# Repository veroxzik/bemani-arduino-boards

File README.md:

# bemani-arduino-boards
 A collection of Arduuino breakout boards and code for Bemani uses.

## How to Order

Download the *.zip file from your chosen Boards/gerbers folder and upload to your PCB manufacturer of choice. JLCPCB is a common suggestion and the one I use most frequently. Default choices are all acceptable.

A list of parts for each board is located in their respective folders.

## Physical Settings on the Boards

Each board has a few physical solder jumpers that you must set before use.

### Setting the lights power source

Locate the jumper labeled CNR PWR | USB PWR. If you wish to power the lights off of USB power, jump the center pad and the USB PWR pad together.

If you wish to use the external power header, jump the center pad and the CNR PWR pad together. All external power headers are such that the square pin is positive.

On several boards, it is necessary to select whether you want to use encoders or buttons. Such option is used by soldering the *two* jumpers between either BUT or ENC.

On the Micro boards, if you use one encoder, it must be QE2. On the Pro Micro board, it must be QE1. (Or you can change my code if you don't like this restriction.)

## How to Flash Firmware

### Load the board profile

Move the folder `Additional Files\arduino-bemani` to your local hardware folder, most commonly located at `Documents\Arduino\hardware\`.
Your final path should look like `Documents\Arduino\hardware\arduino-bemani`.

Start the Arduino IDE / restart if it's already open.

This uses a copy of the Arduino 1.8.1 core, for reference. You should not have to update it.

### Loading the firmware

In the Arduino IDE, select the board using `Tools->Board->Bemani Controller (Micro/Pro Micro)` under the `VXZK Custom Boards` section.

In `Config.h`, set the following parameters per your board and setup.

```c
/* --- --- --- --- --- --- ---
   Frequently Changed Settings
   --- --- --- --- --- --- --- */

// This is the number of encoders you are using.
// If it is 1 and you are using a Micro board, then you must use QE2.
// If it is 1 and you are using a Pro Micro board, then you must use QE1
#define NUM_ENCODERS 0

// This is the PPR of your encoder
// Common values are 600 for Chinese encoders and 24 for Bourns encoders
const uint16_t pulseCount = 24;

// Uncomment the corresponding define for the microcontroller you are using
//#define USE_PROMICRO
//#define USE_MICRO
```

You must uncomment either the USE_PROMICRO or USE_MICRO define or the compiler will throw an error.

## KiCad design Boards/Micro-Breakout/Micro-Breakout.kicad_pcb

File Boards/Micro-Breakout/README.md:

# Micro Breakout

## Description

This board uses the Arduino Micro as its base and supports 4 pin button connectors using the DJ DAO layout.

It is configurable for one of the three options:
1. 12 buttons, no encoders
2. 11 buttons, 1 encoder
3. 10 buttons, 2 encoders

## Bill of Materials

| Part | Description | Qty | Link |
|:---|:---|:---:|:---|
| Arduino Micro | Microprocessor | 1 | Search "Arduino Micro" on Aliexpress, ensure the listing says 32U4. Example listing: https://www.aliexpress.us/item/2251801707415032.html |
| JST XH 4P Header | Connector for buttons, encoders, and RGB | 14 | https://www.lcsc.com/product-detail/Wire-To-Board-Wire-To-Wire-Connector_BOOMELE-Boom-Precision-Elec-XH-4A_C37815.html |
| 2N7000 | MOSFET 60V 0.2A N-Channel TO-92 | 12 | https://www.lcsc.com/product-detail/MOSFETs_Jiangsu-Changjing-Electronics-Technology-Co-Ltd-2N7000_C9114.html |
| JST XH 2P Header | Connector for external power (optional) | 1 (optional) | https://www.lcsc.com/product-detail/Wire-To-Board-Wire-To-Wire-Connector_BOOMELE-Boom-Precision-Elec-XH-2A_C20079.html |

Connectors can also be found on Aliexpress by searching "JST XH".

## Configuration

### Power Selection

Typically, you will be using USB power for this board. Solder the middle and left pads together on jumper located at the top of the board.

By soldering the other two pads, the LEDs will be powered via the JST XH 2P connector. This can allow you to use 12V leds, if this is desired.

### Button and Encoder Selection

Next to each QE connector is a pair of solder jumpers.

To use QE1, solder the middle and top pads together for the marked jumpers. Otherwise, solder the middle and bottom pads to use Button 10.

To use QE2, solder the middle and top pads together for the marked jumpers. Otherwise, solder the middle and bottom pads to use Button 11.

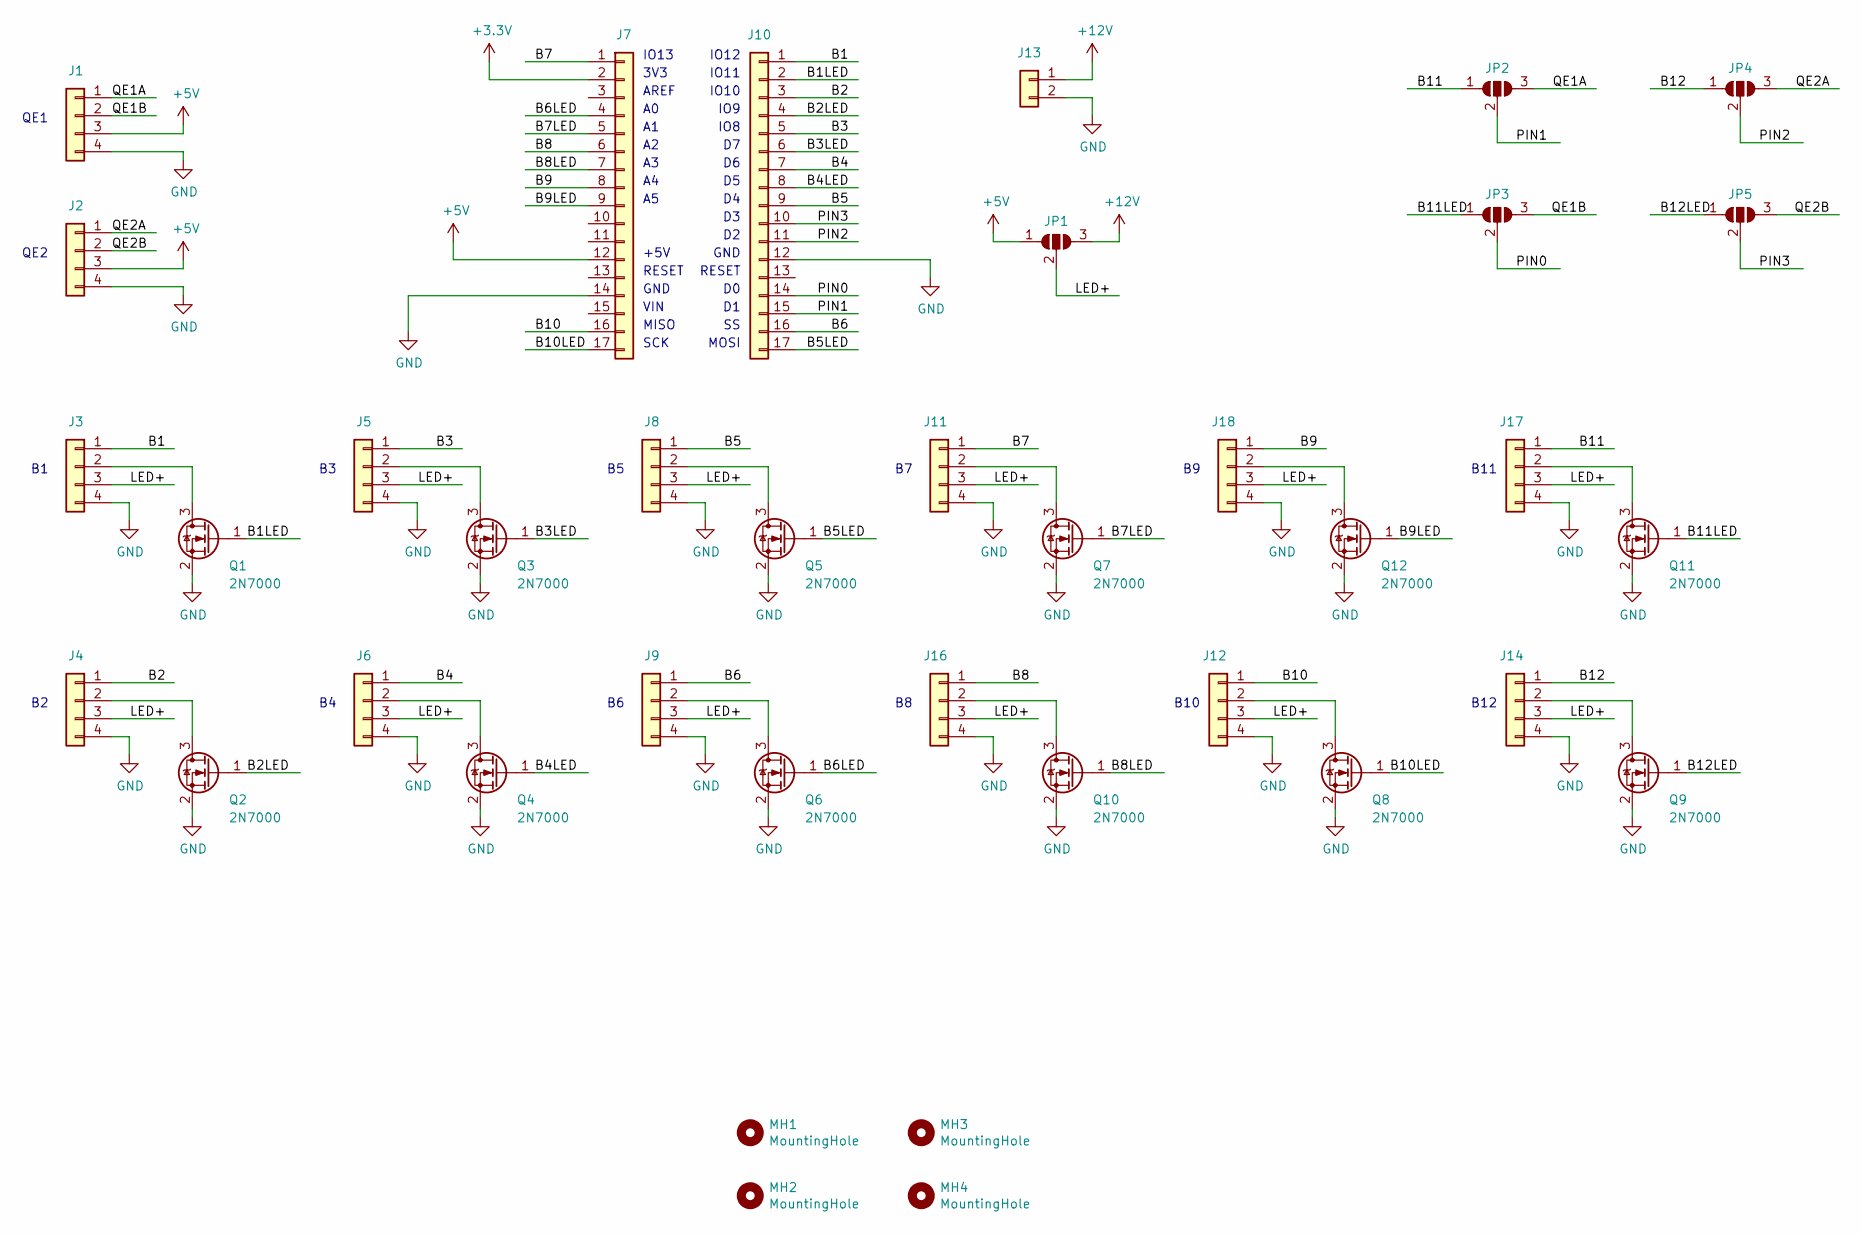
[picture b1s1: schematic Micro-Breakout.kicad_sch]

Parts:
J1, J2, J3, J4, J5, J6, J8, J9, J11, J12, J14, J16, J17, J18: Conn_01x04; JST_XH_B4B-XH-A_1x04_P2.50mm_Vertical
J7, J10: Conn_01x17; PinSocket_1x17_P2.54mm_Vertical
J13: Conn_01x02; JST_XH_B2B-XH-A_1x02_P2.50mm_Vertical
JP1, JP2, JP3, JP4, JP5: SolderJumper_3_Open; SolderJumper-3_P1.3mm_Open_RoundedPad1.0x1.5mm
MH1, MH2, MH3, MH4: MountingHole; MountingHole_3.2mm_M3
Q1, Q2, Q3, Q4, Q5, Q6, Q7, Q8, Q9, Q10, Q11, Q12: 2N7000; TO-92_Inline_Wide

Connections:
+3V3: J7.2
+5V: J1.3, J2.3, J7.12, JP1.1 (A)
+12V: J13.1, JP1.3 (B)
/B1: J3.1, J10.1
/B1LED: J10.2, Q1.1 (G)
/B2: J4.1, J10.3
/B2LED: J10.4, Q2.1 (G)
/B3: J5.1, J10.5
/B3LED: J10.6, Q3.1 (G)
/B4: J6.1, J10.7
/B4LED: J10.8, Q4.1 (G)
/B5: J8.1, J10.9
/B5LED: J10.17, Q5.1 (G)
/B6: J9.1, J10.16
/B6LED: J7.4, Q6.1 (G)
/B7: J7.1, J11.1
/B7LED: J7.5, Q7.1 (G)
/B8: J7.6, J16.1
/B8LED: J7.7, Q10.1 (G)
/B9: J7.8, J18.1
/B9LED: J7.9, Q12.1 (G)
/B10: J7.16, J12.1
/B10LED: J7.17, Q8.1 (G)
/B11: J17.1, JP2.1 (A)
/B11LED: JP3.1 (A), Q11.1 (G)
/B12: J14.1, JP4.1 (A)
/B12LED: JP5.1 (A), Q9.1 (G)
/LED+: J3.3, J4.3, J5.3, J6.3, J8.3, J9.3, J11.3, J12.3, J14.3, J16.3, J17.3, J18.3, JP1.2 (C)
/PIN0: J10.14, JP3.2 (C)
/PIN1: J10.15, JP2.2 (C)
/PIN2: J10.11, JP4.2 (C)
/PIN3: J10.10, JP5.2 (C)
/QE1A: J1.1, JP2.3 (B)
/QE1B: J1.2, JP3.3 (B)
/QE2A: J2.1, JP4.3 (B)
/QE2B: J2.2, JP5.3 (B)
GND: J1.4, J2.4, J3.4, J4.4, J5.4, J6.4, J7.14, J8.4, J9.4, J10.12, J11.4, J12.4, J13.2, J14.4, J16.4, J17.4, J18.4, Q1.2 (S), Q2.2 (S), Q3.2 (S), Q4.2 (S), Q5.2 (S), Q6.2 (S), Q7.2 (S), Q8.2 (S), Q9.2 (S), Q10.2 (S), Q11.2 (S), Q12.2 (S)
unnamed: J3.2, Q1.3 (D)
unnamed: J4.2, Q2.3 (D)
unnamed: J5.2, Q3.3 (D)
unnamed: J6.2, Q4.3 (D)
unnamed: J8.2, Q5.3 (D)
unnamed: J9.2, Q6.3 (D)
unnamed: J11.2, Q7.3 (D)
unnamed: J12.2, Q8.3 (D)
unnamed: J14.2, Q9.3 (D)
unnamed: J16.2, Q10.3 (D)
unnamed: J17.2, Q11.3 (D)
unnamed: J18.2, Q12.3 (D)

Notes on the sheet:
IO11
B12
QE1
QE2
VIN
GND
3V3
IO9
MOSI
+5V
RESET
MISO
SCK
IO8
IO13
B11
IO10
B10
IO12
AREF

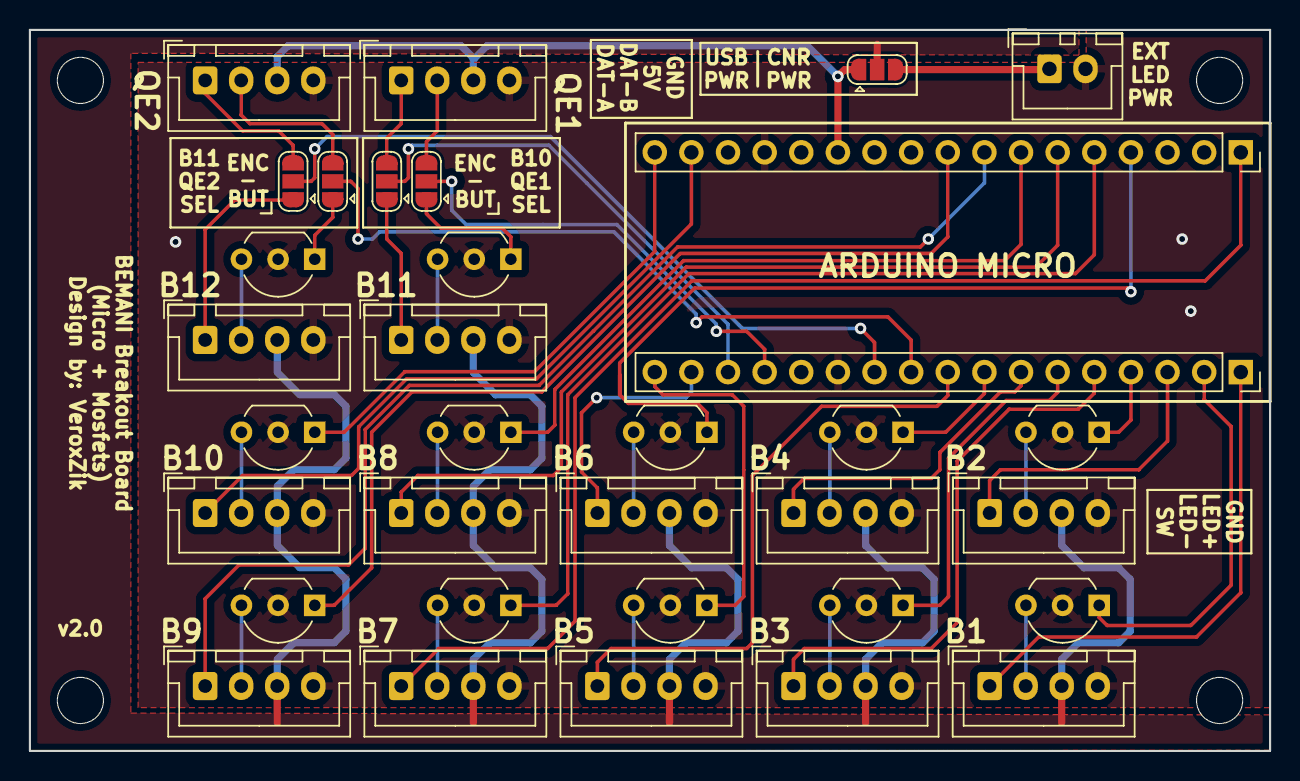
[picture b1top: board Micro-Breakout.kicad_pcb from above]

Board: 2 copper layers, 86.0 x 50.0 mm, 38 parts (0 on the bottom side), 48 nets.

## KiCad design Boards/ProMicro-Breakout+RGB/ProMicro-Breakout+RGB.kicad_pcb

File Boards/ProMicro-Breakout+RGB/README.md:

# ProMicro Breakout + RGB

## Description

This board is just for the bare essentials, providing 12 buttons (WITHOUT lights), 2 quadrature encoder inputs, and 1 ARGB header.

## Bill of Materials

| Part | Description | Qty | Link |
|:---|:---|:---:|:---|
| Arduino Pro Micro | Microprocessor | 1 | Search "Pro Micro" on Aliexpress, ensure the listing says 32U4 |
| JST XH 2P Header | Connector for buttons and power (optional) | 12 (+ 1 optional) | https://www.lcsc.com/product-detail/Wire-To-Board-Wire-To-Wire-Connector_BOOMELE-Boom-Precision-Elec-XH-2A_C20079.html |
| JST XH 4P Header | Connector for encoder and RGB | 3 | https://www.lcsc.com/product-detail/Wire-To-Board-Wire-To-Wire-Connector_BOOMELE-Boom-Precision-Elec-XH-4A_C37815.html |

Connectors can also be found on Aliexpress by searching "JST XH".

## Configuration

### Power Selection

Typically, you will be using USB power for this board. Solder the middle and right pads together on jumper JP1.

By soldering the other two pads, the LEDs will be powered via the JST XH 2P connector. This can allow you to use 12V leds, if this is desired.

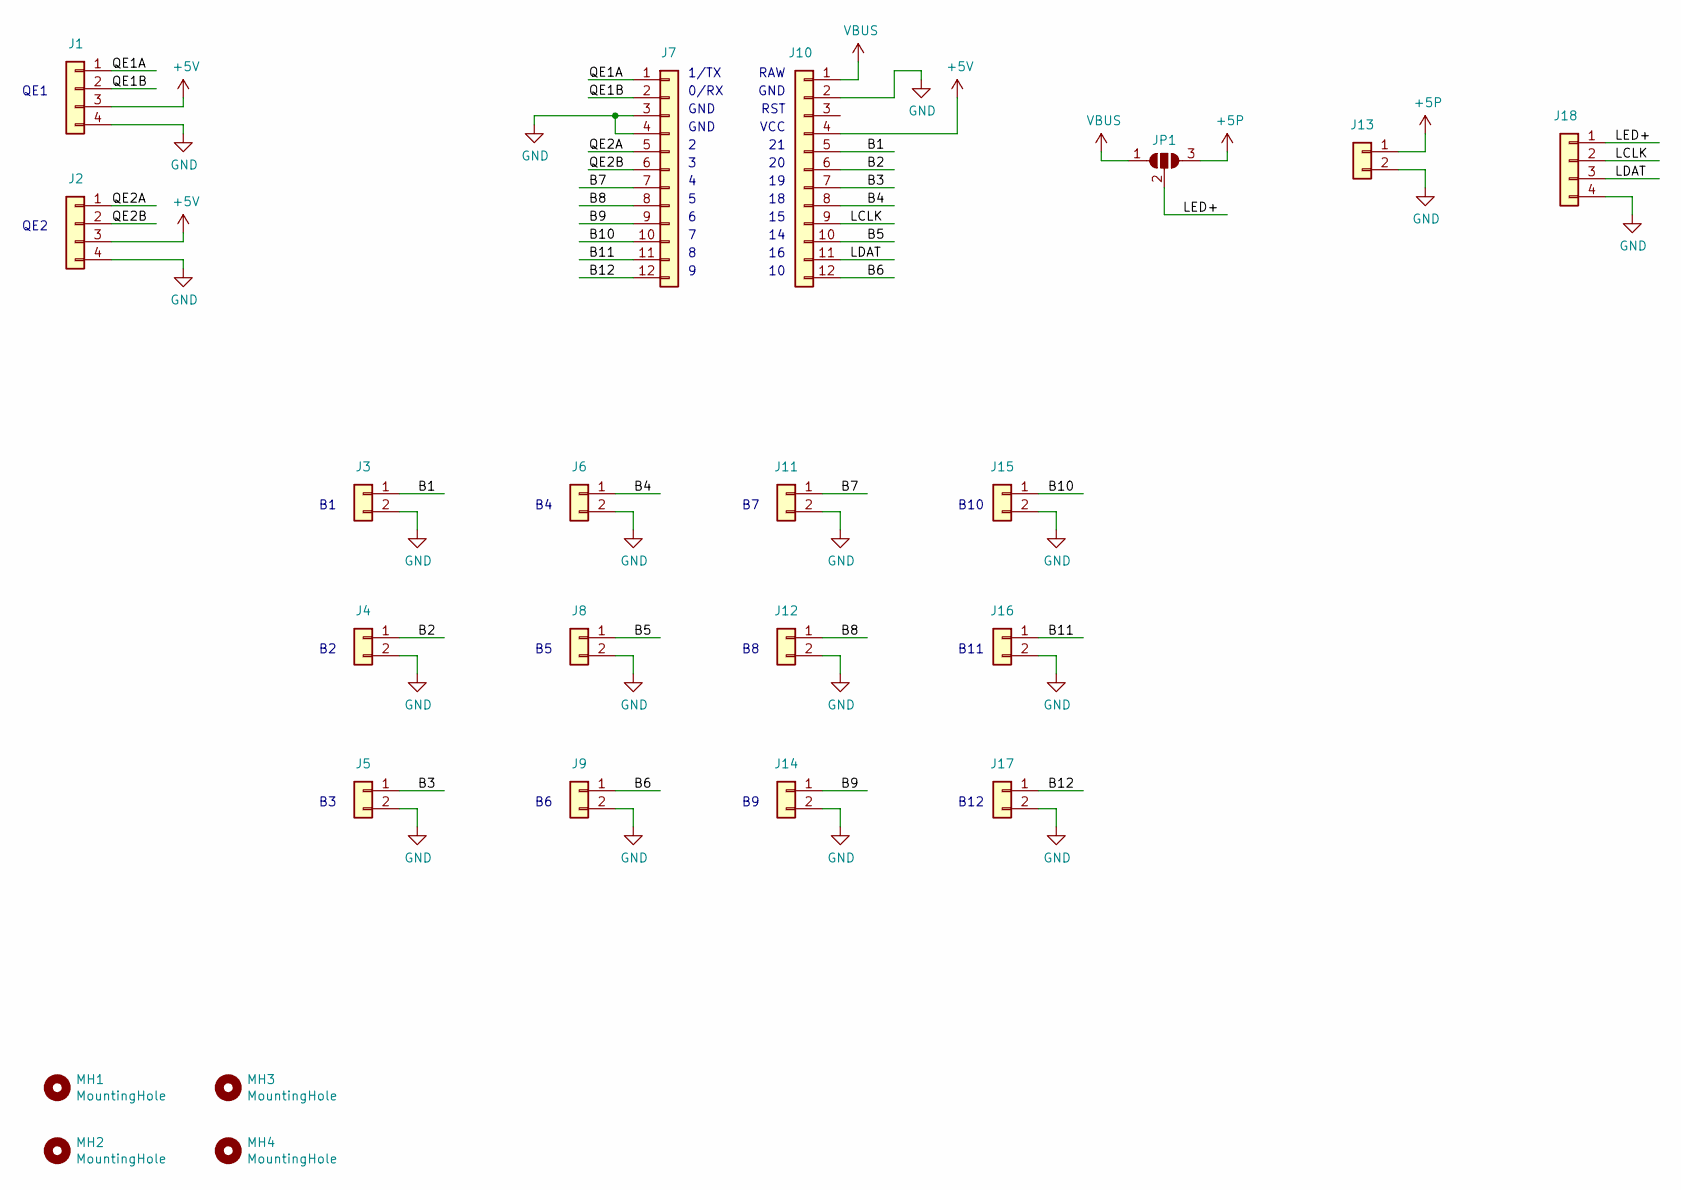
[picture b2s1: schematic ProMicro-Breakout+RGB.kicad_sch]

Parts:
J1, J2, J18: Conn_01x04; JST_XH_B04B-XH-A_04x2.50mm_Straight
J3, J4, J5, J6, J8, J9, J11, J12, J13, J14, J15, J16, J17: Conn_01x02; JST_XH_B02B-XH-A_02x2.50mm_Straight
J7, J10: Conn_01x12; PinSocket_1x12_P2.54mm_Vertical
JP1: SolderJumper_3_Open; SolderJumper-3_P1.3mm_Open_RoundedPad1.0x1.5mm
MH1, MH2, MH3, MH4: MountingHole; MountingHole_3.2mm_M3

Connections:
+5P: J13.1, JP1.3 (B)
+5V: J1.3, J2.3, J10.4
/B1: J3.1, J10.5
/B2: J4.1, J10.6
/B3: J5.1, J10.7
/B4: J6.1, J10.8
/B5: J8.1, J10.10
/B6: J9.1, J10.12
/B7: J7.7, J11.1
/B8: J7.8, J12.1
/B9: J7.9, J14.1
/B10: J7.10, J15.1
/B11: J7.11, J16.1
/B12: J7.12, J17.1
/LCLK: J10.9, J18.2
/LDAT: J10.11, J18.3
/LED+: J18.1, JP1.2 (C)
/QE1A: J1.1, J7.1
/QE1B: J1.2, J7.2
/QE2A: J2.1, J7.5
/QE2B: J2.2, J7.6
GND: J1.4, J2.4, J3.2, J4.2, J5.2, J6.2, J7.3, J7.4, J8.2, J9.2, J10.2, J11.2, J12.2, J13.2, J14.2, J15.2, J16.2, J17.2, J18.4
VBUS: J10.1, JP1.1 (A)

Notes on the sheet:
B12
QE2
B11
GND
B10
0/RX
VCC
QE1
1/TX
RST
RAW

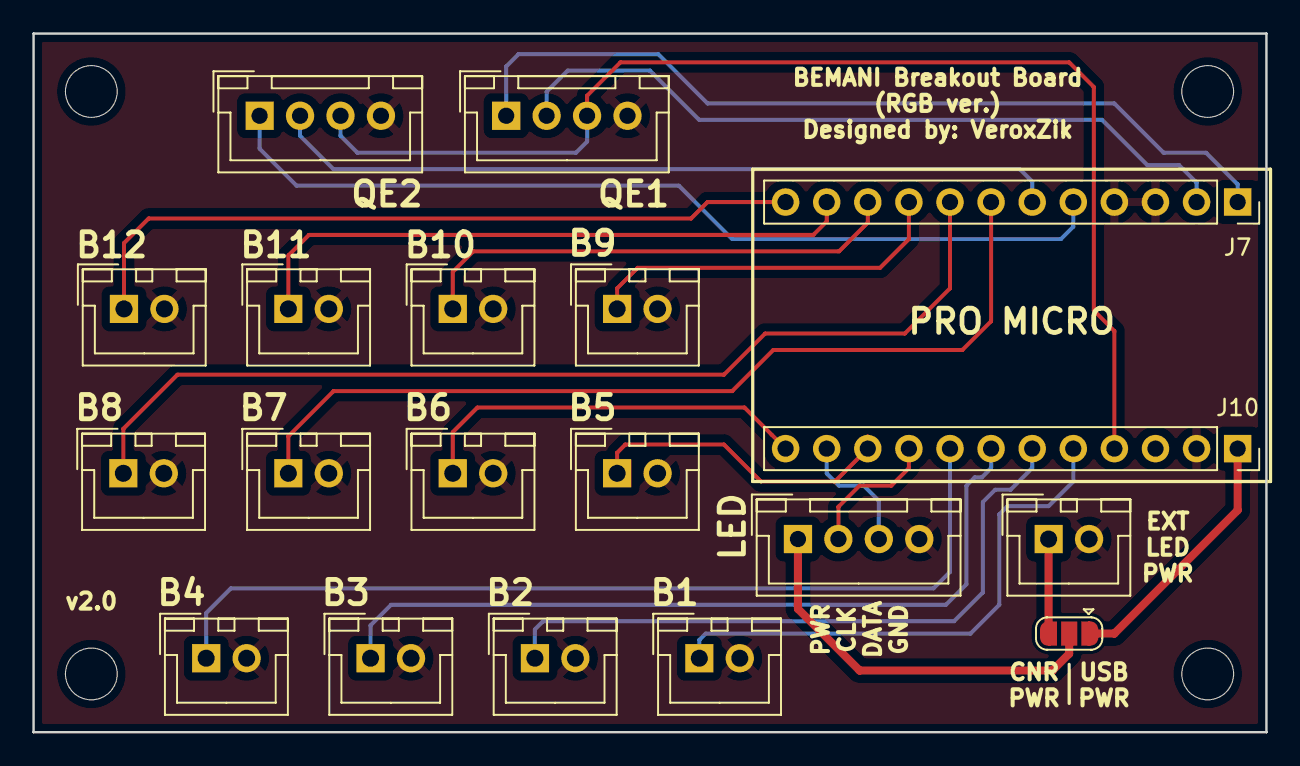
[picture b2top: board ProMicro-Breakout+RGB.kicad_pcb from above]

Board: 2 copper layers, 76.2 x 43.2 mm, 23 parts (0 on the bottom side), 23 nets.

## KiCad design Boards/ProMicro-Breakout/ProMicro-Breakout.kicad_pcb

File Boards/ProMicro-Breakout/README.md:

# ProMicro Breakout

## Description

This board uses the Sparkfun Pro Micro as its base and supports 4 pin button connectors using the DJ DAO layout.

It is configurable for one of the three options:
1. 9 buttons, no encoders
2. 8 buttons, 1 encoder
3. 7 buttons, 2 encoders

## Bill of Materials

| Part | Description | Qty | Link |
|:---|:---|:---:|:---|
| Arduino Pro Micro | Microprocessor | 1 | Search "Pro Micro" on Aliexpress, ensure the listing says 32U4 |
| JST XH 4P Header | Connector for buttons and encoder | 11 | https://www.lcsc.com/product-detail/Wire-To-Board-Wire-To-Wire-Connector_BOOMELE-Boom-Precision-Elec-XH-4A_C37815.html |
| JST XH 2P Header | Connector for external power (optional) | 1 (optional) | https://www.lcsc.com/product-detail/Wire-To-Board-Wire-To-Wire-Connector_BOOMELE-Boom-Precision-Elec-XH-2A_C20079.html |
| 2N7000 | MOSFET 60V 0.2A N-Channel TO-92 | 9 | https://www.lcsc.com/product-detail/MOSFETs_Jiangsu-Changjing-Electronics-Technology-Co-Ltd-2N7000_C9114.html |

Connectors can also be found on Aliexpress by searching "JST XH".

## Configuration

### Power Selection

Typically, you will be using USB power for this board. Solder the middle and right pads together on jumper JP1.

By soldering the other two pads, the LEDs will be powered via the JST XH 2P connector. This can allow you to use 12V leds, if this is desired.

### Button and Encoder Selection

Next to each QE connector is a pair of solder jumpers.

To use QE1, solder the middle and right pads together for jumpers JP2 and JP3. Otherwise, solder the middle and left pads to use Button 9.

To use QE2, solder the middle and right pads together for jumpers JP4 and JP5. Otherwise, solder the middle and left pads to use Button 8.

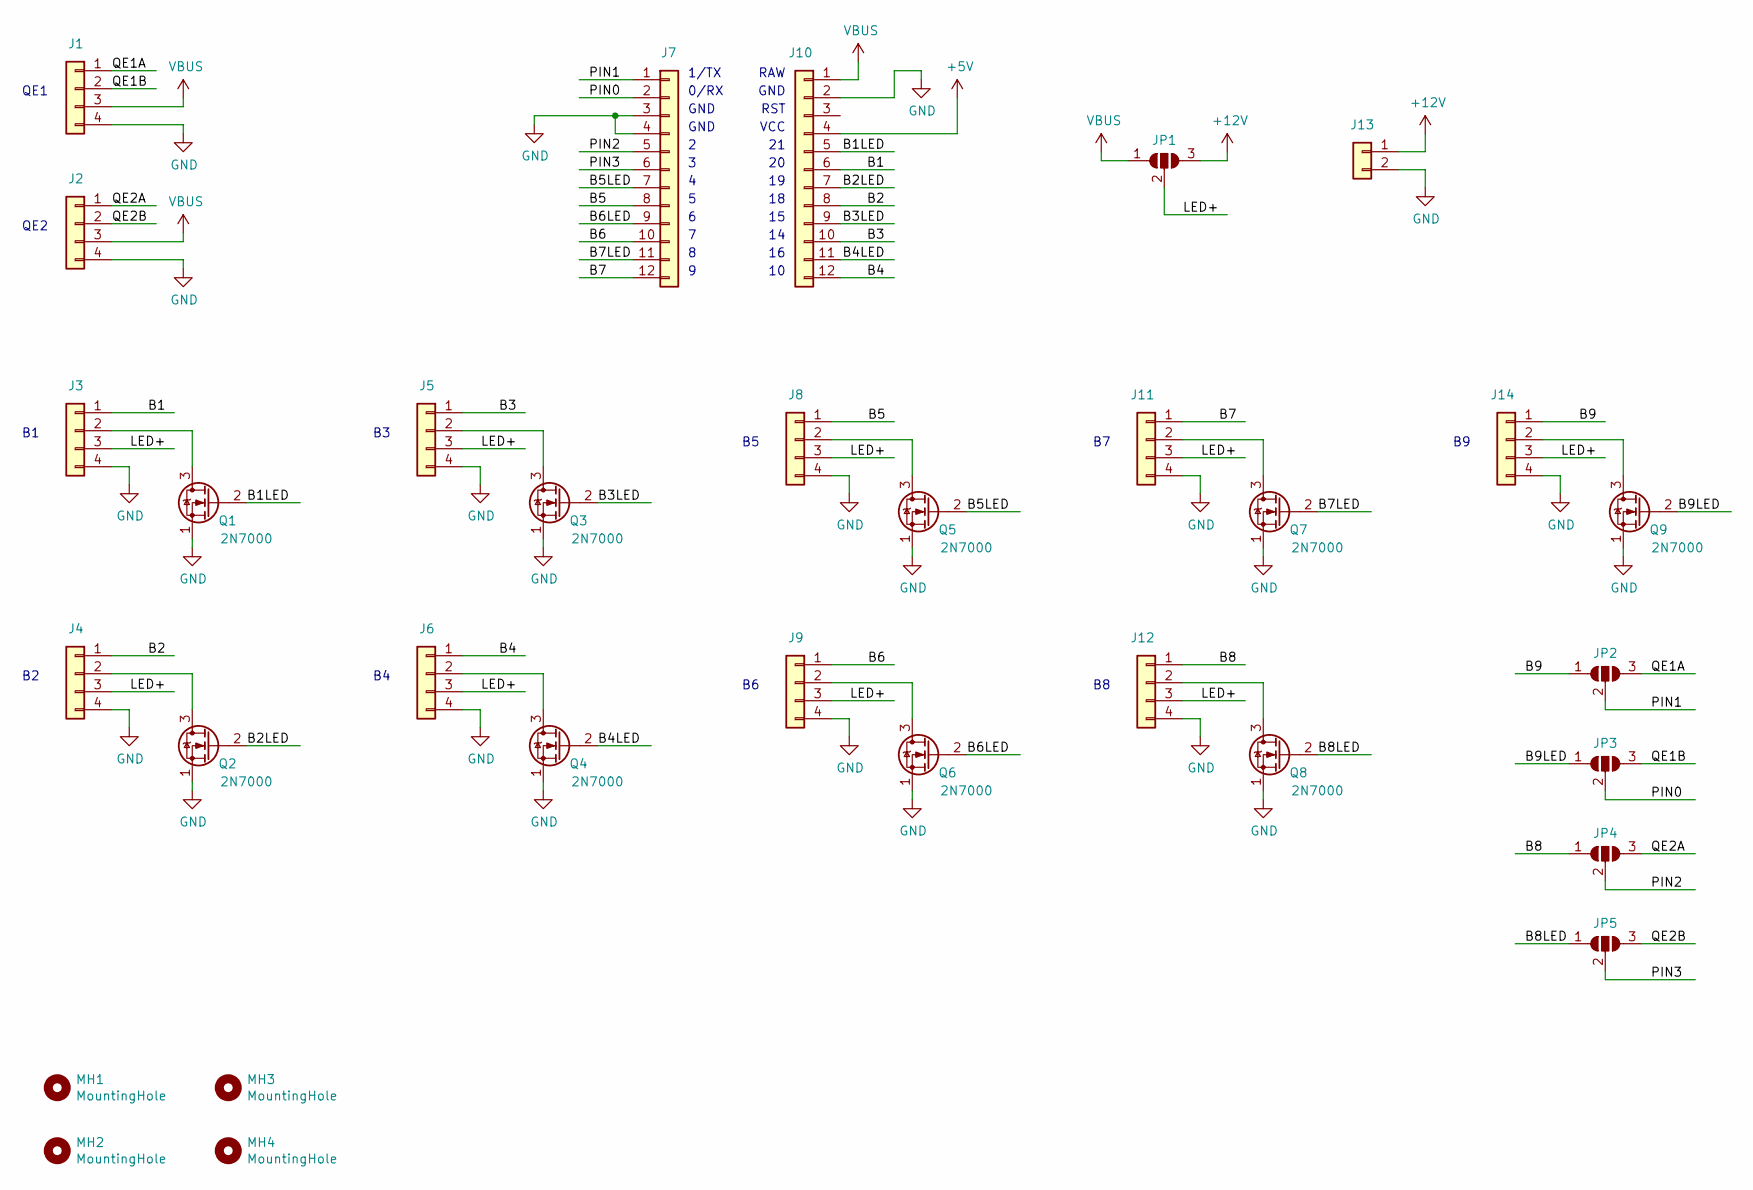
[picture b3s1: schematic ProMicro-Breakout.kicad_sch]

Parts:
J1, J2, J3, J4, J5, J6, J8, J9, J11, J12, J14: Conn_01x04; JST_XH_B04B-XH-A_04x2.50mm_Straight
J7, J10: Conn_01x12; PinSocket_1x12_P2.54mm_Vertical
J13: Conn_01x02; JST_XH_B02B-XH-A_02x2.50mm_Straight
JP1, JP2, JP3, JP4, JP5: SolderJumper_3_Open; SolderJumper-3_P1.3mm_Open_RoundedPad1.0x1.5mm
MH1, MH2, MH3, MH4: MountingHole; MountingHole_3.2mm_M3
Q1, Q2, Q3, Q4, Q5, Q6, Q7, Q8, Q9: 2N7000; TO-92_Inline_Wide

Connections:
+5V: J10.4
+12V: J13.1, JP1.3 (B)
/B1: J3.1, J10.6
/B1LED: J10.5, Q1.2 (G)
/B2: J4.1, J10.8
/B2LED: J10.7, Q2.2 (G)
/B3: J5.1, J10.10
/B3LED: J10.9, Q3.2 (G)
/B4: J6.1, J10.12
/B4LED: J10.11, Q4.2 (G)
/B5: J7.8, J8.1
/B5LED: J7.7, Q5.2 (G)
/B6: J7.10, J9.1
/B6LED: J7.9, Q6.2 (G)
/B7: J7.12, J11.1
/B7LED: J7.11, Q7.2 (G)
/B8: J12.1, JP4.1 (A)
/B8LED: JP5.1 (A), Q8.2 (G)
/B9: J14.1, JP2.1 (A)
/B9LED: JP3.1 (A), Q9.2 (G)
/LED+: J3.3, J4.3, J5.3, J6.3, J8.3, J9.3, J11.3, J12.3, J14.3, JP1.2 (C)
/PIN0: J7.2, JP3.2 (C)
/PIN1: J7.1, JP2.2 (C)
/PIN2: J7.5, JP4.2 (C)
/PIN3: J7.6, JP5.2 (C)
/QE1A: J1.1, JP2.3 (B)
/QE1B: J1.2, JP3.3 (B)
/QE2A: J2.1, JP4.3 (B)
/QE2B: J2.2, JP5.3 (B)
GND: J1.4, J2.4, J3.4, J4.4, J5.4, J6.4, J7.3, J7.4, J8.4, J9.4, J10.2, J11.4, J12.4, J13.2, J14.4, Q1.1 (S), Q2.1 (S), Q3.1 (S), Q4.1 (S), Q5.1 (S), Q6.1 (S), Q7.1 (S), Q8.1 (S), Q9.1 (S)
unnamed: J3.2, Q1.3 (D)
unnamed: J4.2, Q2.3 (D)
unnamed: J5.2, Q3.3 (D)
unnamed: J6.2, Q4.3 (D)
unnamed: J8.2, Q5.3 (D)
unnamed: J9.2, Q6.3 (D)
unnamed: J11.2, Q7.3 (D)
unnamed: J12.2, Q8.3 (D)
unnamed: J14.2, Q9.3 (D)
VBUS: J1.3, J2.3, J10.1, JP1.1 (A)

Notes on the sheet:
RAW
RST
QE1
GND
QE2
1/TX
VCC
0/RX

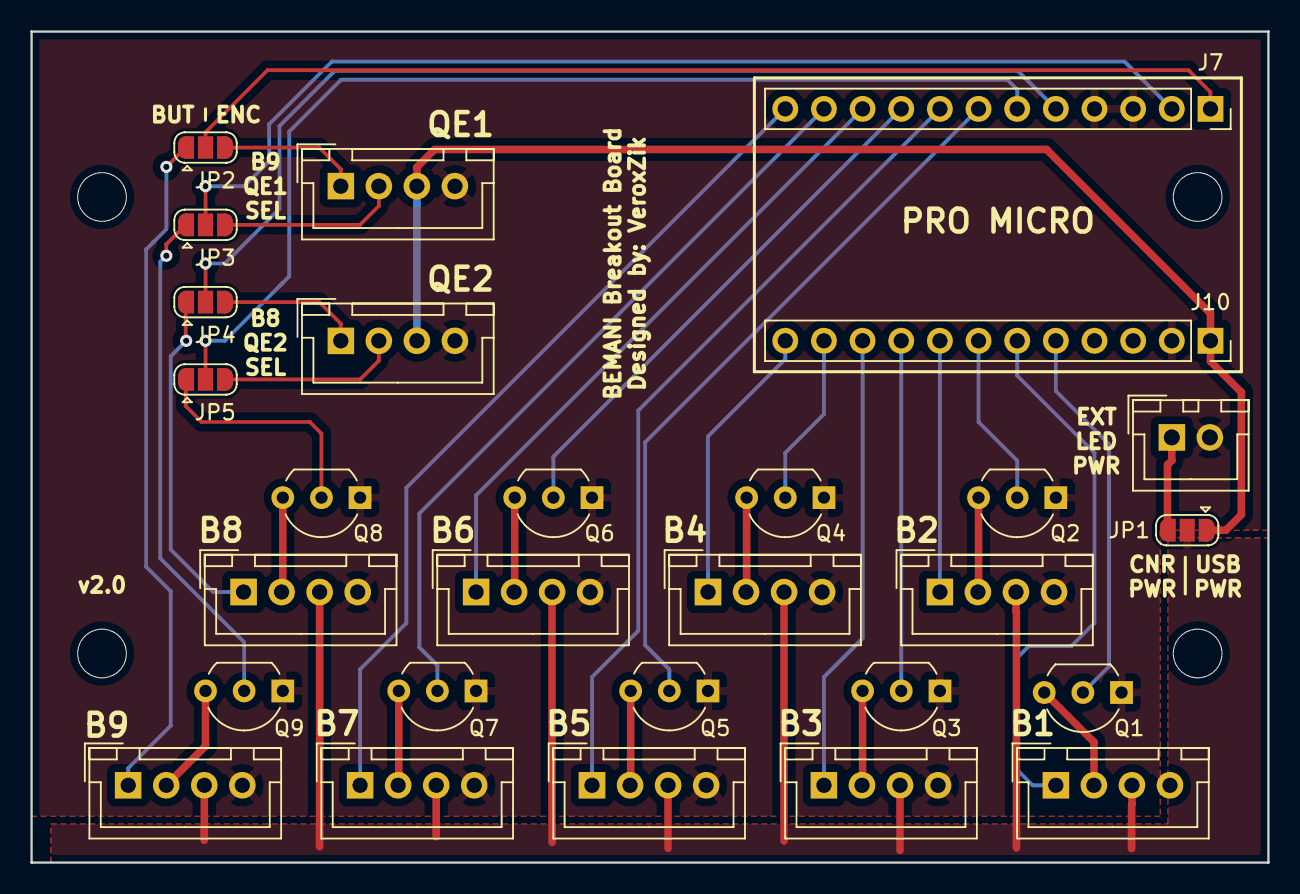
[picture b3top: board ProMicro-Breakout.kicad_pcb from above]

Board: 2 copper layers, 81.3 x 54.6 mm, 32 parts (0 on the bottom side), 39 nets.

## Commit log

2019-10-27 Initial Commit
    Includes:
    Pro Micro Single LED board
    Pro Micro RGB board
    Micro Single LED board
2019-10-27 Fixed broken trace on Micro Breakout
2019-10-27 Fixed Micro-Breakout filenames
2019-10-27 Adds Micro Breakout RGB version
2019-12-12 Changes license to GPL v3.0
2019-12-19 Uploaded firmware and modified core files
2020-01-31 Fixed Encoder
    Was broken for PPR > 255 / in general
2020-01-31 Fixed Lights
    Forgot to set pins to output
2020-01-31 Added Micro RGB pinout to code, fixed lights (again)
2020-02-01 Added mouse mode
2020-02-01 Add reactive lights
2020-02-01 Added discrete KBM and Joystick modes
2020-02-21 Update both micro boards to v1.1
    Fixes 5V on the LED connector
    Adds pinout labels for Encoder / Button connectors
2020-05-31 Update Micro-RGB to v1.2
    This shifts the SS and MISO pins to B9 in an attempt to consolidate potentially nonfunctional pins while using the SPI port for RGB functionality.
2020-09-25 Updated Firmware, Added schematic PDF
    Adds support for the Turbocharger+ LED boards
2020-09-25 Adds Arduino SPI library
2023-02-12 Update ProMicro-Breakout board.
2023-02-12 Update ProMicro-Breakout+RGB board.
2023-02-12 Update MicroBreakout+RGB board.
2023-02-13 Update Micro-Breakout board.
2023-02-13 Add overall board README and move all old boards to archive.
2023-02-13 Add "How to Order" to README.
2024-04-28 Adds spoof configs to the library
